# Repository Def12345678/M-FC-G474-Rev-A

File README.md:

# M-FC — Modular Flight Controller (REV-1)

> **Note:** This is REV-1 — a Proof-of-Concept / educational build. REV-2 is in development and will address known hardware ergonomics issues. Not recommended for production use.

M-FC has been flying on a 5" freestyle build for over a year.

---

## Overview

M-FC is a DIY flight controller designed for FPV drones 30.5x30.5mm mounting holes, built around the STM32G474RET6 microcontroller and running Betaflight 4.6. The "Modular" name reflects the connector philosophy — every peripheral interface is broken out via JST-SH connectors, making wiring clean, repeatable, and swap-friendly.

The board is paired with a dedicated PDB in a standard FC/PDB stack configuration. The FC itself operates at 5V (no onboard BEC), sourcing power from the ESC or PDB. REV-2 will include an onboard BEC.

---

## Hardware Specifications

| Component | Details |
|---|---|
| **MCU** | STM32G474RET6 |
| **IMU** | ICM-42688-P (SPI2) |
| **Barometer** | DPS368 (I2C4) |
| **Magnetometer** | Not populated |
| **OSD** | AT7456E (SPI1) |
| **Blackbox Flash** | W25Q128JVSIQ — 16 MB (SPI3) |
| **USB** | USB-C (with detect on PA10) |
| **Mounting** | 30.5 × 30.5 mm |
| **Input Voltage** | 5V (no onboard BEC — requires 5V from ESC or PDB) |

### Power Architecture

The FC does not regulate voltage from the battery. **5V must be supplied externally** — either from an ESC BEC or from the PDB — via the dedicated 5V pads on the board.

Two separate LDO regulators are present onboard:
- One for the MCU
- One for sensors (IMU, barometer)

A **Schottky diode** is used to isolate USB power from battery power. When powered via USB only, the FC supplies power exclusively to the MCU, sensors (IMU, barometer), OSD chip, flash, GPS, and RX. All remaining peripherals (motors, VTX, etc.) are only powered when the battery is connected via the PDB.

### PDB (Stack)

| Parameter | Value |
|---|---|
| **Max continuous current** | ~120 A total |
| **Per-motor channel** | ~30 A |
| **Configuration** | FC + PDB stack |

The FC connects to the PDB via an 8-pin JST-SH connector plus dedicated `5V_IN` and `GND` solder pads. The `5V_IN` pad powers the FC only — it does not back-feed to the PDB rail.

The PDB includes:
- **5V buck converter** — 2.5 A output
- **9V buck converter** — 2.5 A output (configurable to 12V by replacing resistor R5 — refer to the schematic for the correct resistor value via the linked Texas Instruments buck calculator)

Each ESC must be connected through the PDB. The `VBAT` pin on the 8-pin JST-SH outputs a voltage-divided signal safe for the MCU ADC, used for battery voltage monitoring in Betaflight.

---

## Connector Pinout

All peripheral connections use JST-SH connectors.

| Connector | Pins | Interface | Notes |
|---|---|---|---|
| **ESC** | 8 | DSHOT + telemetry | Motors 1–4 |
| **RX** | 4 | UART | RC receiver |
| **CAM** | 3 | Camera control | Analog camera |
| **VTX** | 4 | UART | Video transmitter |
| **GPS** | 6 | UART + I2C | GPS + compass |
| **LED** | 3 | LED strip | Addressable LEDs |

### Additional Exposed Pads

- **5V input pads** — mandatory external 5V supply
- **PWM 1–3** — additional PWM outputs
- **UART breakout** — spare UART pads
- **I2C breakout** — spare I2C pads

### Photos & Pinout Diagrams

Additional renders, routing views, and PCB previews are available in the [`img/`](img/) folder.

---

## Betaflight Target

- **Betaflight version:** 4.6
- **Target name:** `M-FC`
- **MCU family:** `STM32G47X`

Pre-compiled firmware (`.hex`) and the target config file are included in this repository. The hex supports all features listed below.

### Enabled Features

| Feature | Detail |
|---|---|
| Gyroscope / Accelerometer | ICM-42688-P via SPI2 |
| Barometer | DPS368 via I2C4 |
| Blackbox | W25Q128FV via SPI3, default device |
| OSD | MAX7456 (AT7456E) via SPI1 |
| Motors | DSHOT bitbang, pins PA0–PA3 |
| LED strip | PC0 |
| Buzzer | PC3 (inverted) |
| Debug LEDs | PB6, PB7, PB9 |
| VBAT ADC | PC1 |
| Current ADC | PC2 |
| Camera control | PB0 |
| GPS | Enabled |
| Magnetometer | Enabled (I2C2) |
| Position hold | Enabled |
| Altitude hold | Enabled |

### UART Map

| UART | TX | RX | Suggested Use |
|---|---|---|---|
| UART1 | PC4 | PC5 | — |
| UART3 | PB10 | PB11 | — |
| UART4 | PC10 | PC11 | — |
| UART5 | PC12 | PD2 | — |

### I2C Map

| Bus | SCL | SDA | Used for |
|---|---|---|---|
| I2C2 | PA8 | PA9 | Magnetometer |
| I2C3 | PC8 | PC9 | — |
| I2C4 | PC6 | PC7 | Barometer (DPS368) |

### Motor Timer Map

| Index | Pin | Timer | Channel |
|---|---|---|---|
| Motor 1 | PA0 | TIM2 | CH1 |
| Motor 2 | PA1 | TIM2 | CH2 |
| Motor 3 | PA2 | TIM2 | CH3 |
| Motor 4 | PA3 | TIM2 | CH4 |
| CC | PB0 | TIM3 | CH3 |
| LED strip | PC0 | — | CH1 |

---

## Flashing Firmware

### Pre-compiled hex

1. Download the `.hex` file from this repository.
2. Open **Betaflight Configurator 10.10+**.
3. Enter DFU mode — hold the boot button while plugging in USB-C, or send `bl` via CLI.
4. In the **Firmware Flasher** tab, select **Load Firmware [Local]** and pick the `.hex`.
5. Flash. Avoid **Full chip erase** unless necessary.

### Building from source

You can compile your own firmware with custom flags. Copy the target config file into the `configs/` folder of the Betaflight source tree, then build normally.

Building was tested using WSL. Refer to the official Betaflight build guide for setup instructions:
[https://betaflight.com/docs/development/building/Building-in-Ubuntu](https://betaflight.com/docs/development/building/Building-in-Ubuntu)

## Flight Logs & Blackbox Data

Blackbox logs and DVR footage from test flights are available in the [`logs/`](logs/) folder and on https://youtu.be/7Q5jRaf4V_Y(#) / https://pixeldrain.com/u/gxZJVt8E(#).

Logs were recorded using the onboard W25Q128JVSIQ flash via Betaflight 4.6 blackbox at 1kHz.

## Test build
| Component | Details |
|---|---|
| **ESC** | LittleBee Spring 30A (BlueJay firmware) |
| **VTX** | SpeedyBee TX800 (Pagoda2) |
| **RX** | SpeedyBee Nano ELRS |
| **Camera** | Mista 1672 |
| **Motors** | Emax RS2205 2350KV |
| **Battery** | 4S 1550mAh (Ovionic) |
| **Frame** | Geprc MK4 5" |

---

## Known Issues (REV-1)

- **Connector placement ergonomics** — JST-SH connectors are not optimally positioned for clean cable routing in a standard stack build. This is the primary driver for REV-2.
- **Betaflight 4.5 blackbox bug** — Blackbox was unreliable on Betaflight 4.5. Betaflight 4.6 resolves this; use 4.6 or later.
- **No onboard 5V BEC** — Requires external 5V source from ESC or PDB.

---

## Planned Changes (REV-2)

- Revised connector layout for improved cable management
- Onboard 5V BEC
- Additional ergonomic improvements based on REV-1 testing

---

## Acknowledgements

Thanks to [@awocrf](https://github.com/awocrf) for reviewing the schematic for correctness and readability, and for helping with PCB layout aesthetics.

---

## License

This project is released under the **MIT License**. See [LICENSE](LICENSE) for details.

Firmware is based on [Betaflight](https://github.com/betaflight/betaflight), licensed under **GPLv3**.

---

## Contributing

This is currently a personal/educational project. REV-2 is in active development. Issues and suggestions are welcome via GitHub Issues.

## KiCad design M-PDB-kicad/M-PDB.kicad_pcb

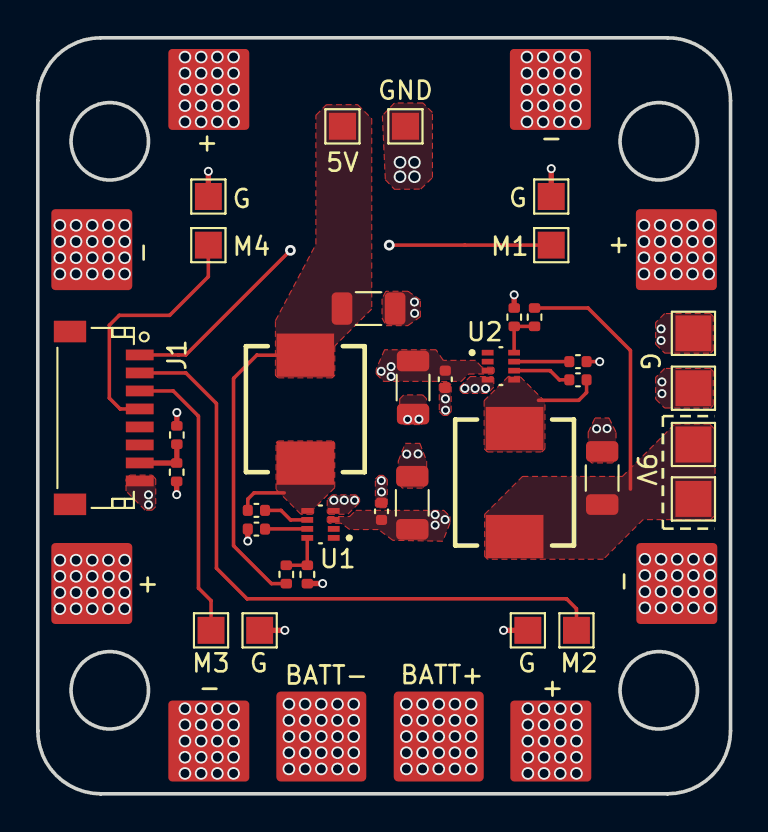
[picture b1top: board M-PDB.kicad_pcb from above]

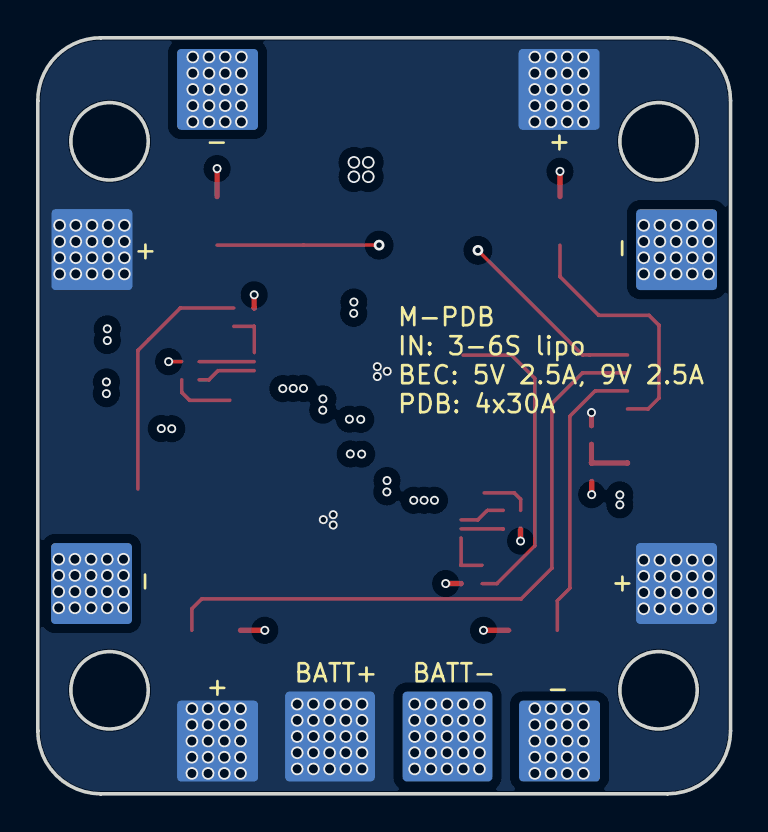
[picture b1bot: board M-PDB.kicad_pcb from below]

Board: 4 copper layers, 38.5 x 42.0 mm, 55 parts (10 on the bottom side), 17 nets.

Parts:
C1, C3, C6, C8: 100n; C_0402_1005Metric
C2, C4, C7, C9: 10u; C_1206_3216Metric
C5, C10: 33n; C_0402_1005Metric
J1: FC Conn; JST_SH_SM08B-SRSS-TB_08x1.00mm_Angled
L1: 6u8; IND-SMD_L7.0-W6.6
L2: 10u; IND-SMD_L7.0-W6.6
PAD1, PAD7: 12V; TestPoint_Pad_2.0x2.0mm
PAD2, PAD8: GND; TestPoint_Pad_2.0x2.0mm
PAD3: M1; TestPoint_Pad_1.5x1.5mm
PAD4, PAD6, PAD10, PAD12, PAD14: GND; TestPoint_Pad_1.5x1.5mm
PAD5: M2; TestPoint_Pad_1.5x1.5mm
PAD9: M3; TestPoint_Pad_1.5x1.5mm
PAD11: M4; TestPoint_Pad_1.5x1.5mm
PAD13: 5V; TestPoint_Pad_1.5x1.5mm
PAD15, PAD15#2: BATT+; pad5x5
PAD16, PAD16#2: BATT-; pad5x5
PAD17, PAD17#2: M1_PWR+; pad4.5
PAD18, PAD18#2: M1_PWR-; pad4.5
PAD19, PAD19#2: M3_PWR+; pad4.5
PAD20, PAD20#2: M3_PWR-; pad4.5
PAD21, PAD21#2: M2_PWR+; pad4.5
PAD22, PAD22#2: M2_PWR-; pad4.5
PAD23, PAD23#2: M4_PWR+; pad4.5
PAD24, PAD24#2: M4_PWR-; pad4.5
R1: 100K; R_0402_1005Metric
R2: 52K3; R_0402_1005Metric
R3, R4, R6: 10K; R_0402_1005Metric
R5: 102K; R_0402_1005Metric
U1, U2: TPS62933DRLR; SOTFL50P160X60-8N

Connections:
+5V: C4.1, L1.2, PAD13.1, R2.1
+9V: C9.1, L2.2, PAD1.1, PAD7.1, R5.1
+VBAT: C2.1, C3.1, C7.1, C8.1, PAD15.1, PAD15#2.1, PAD17.1, PAD17#2.1, PAD19.1, PAD19#2.1, PAD21.1, PAD21#2.1, PAD23.1, PAD23#2.1, R1.1, U1.3 (VIN), U2.3 (VIN)
/ADC_VBAT: J1.7, R1.2, R3.1
/BUCK2_BST: C6.1, U2.6 (BST)
/BUCK2_FB: R5.2, R6.1, U2.8 (FB)
/BUCK2_SS: C10.1, U2.7 (SS)
/BUCK2_SW: C6.2, L2.1, U2.5 (SW)
/BUCK_BST: C1.1, U1.6 (BST)
/BUCK_FB: R2.2, R4.1, U1.8 (FB)
/BUCK_SS: C5.1, U1.7 (SS)
/BUCK_SW: C1.2, L1.1, U1.5 (SW)
GND: C2.2, C3.2, C4.2, C5.2, C7.2, C8.2, C9.2, C10.2, J1.8, PAD2.1, PAD4.1, PAD6.1, PAD8.1, PAD10.1, PAD12.1, PAD14.1, PAD16.1, PAD16#2.1, PAD18.1, PAD18#2.1, PAD20.1, PAD20#2.1, PAD22.1, PAD22#2.1, PAD24.1, PAD24#2.1, R3.2, R4.2, R6.2, U1.4 (GND), U2.4 (GND)
M1: J1.1, PAD3.1
M2: J1.2, PAD5.1
M3: J1.3, PAD9.1
M4: J1.4, PAD11.1

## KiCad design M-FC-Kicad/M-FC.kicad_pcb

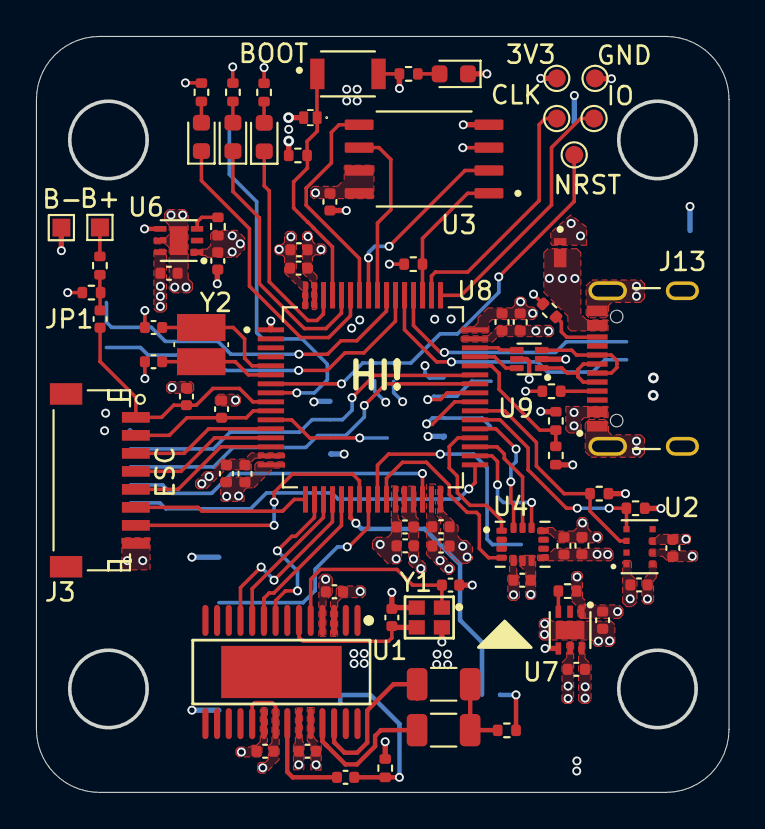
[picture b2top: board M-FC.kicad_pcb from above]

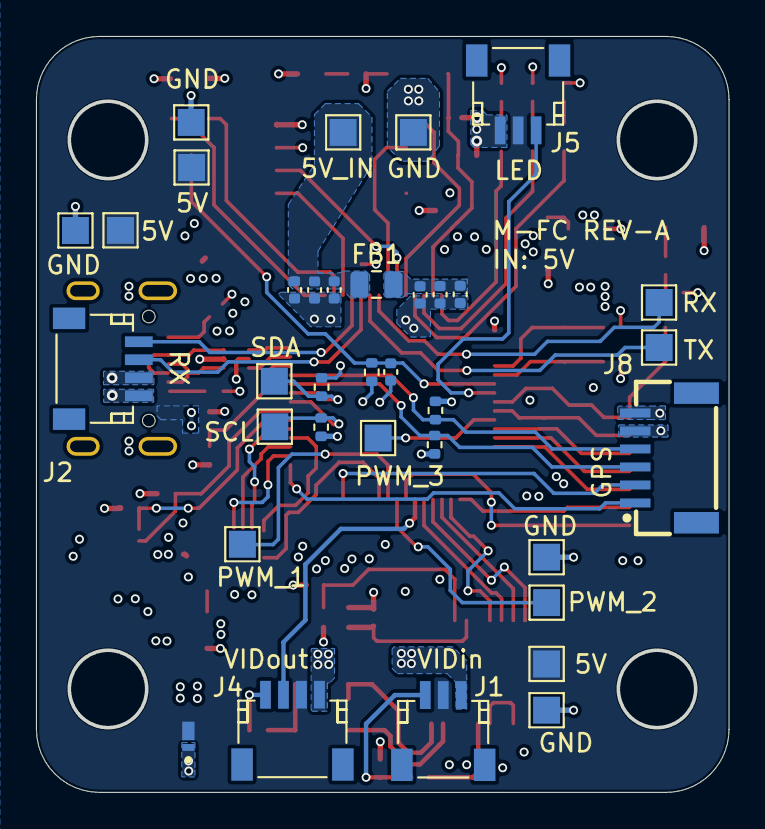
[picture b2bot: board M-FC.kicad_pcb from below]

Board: 4 copper layers, 38.5 x 42.0 mm, 112 parts (35 on the bottom side), 76 nets.

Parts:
C1, C2, C3, C4, C5, C6, C11, C13, C20, C30, C31, C32, C33, C34, C35, C36, C37, C38, C43: 100n; C_0402_1005Metric
C7, C8: 47u; C_1206_3216Metric
C9, C10, C39, C40: 10p; C_0402_1005Metric
C12: 2p2; C_0402_1005Metric
C14, C41, C42: 10n; C_0402_1005Metric
C19, C22, C24, C44: 10u; C_0402_1005Metric
C23, C25, C26, C27, C28, C29: 1u; C_0402_1005Metric
D1, D2: SDM2U30CSP-7B; DIO_SDM2U40CSP-7B
D10: Blue; LED_0603_1608Metric
D11: Green; LED_0603_1608Metric
D12: Amber; LED_0603_1608Metric
D14: ESD; ESDALC6V1-1U2
D18: RED; LED_0603_1608Metric
FB1: 300R; C_0805_2012Metric
J1: CAM; JST_SH_SM03B-SRSS-TB_03x1.00mm_Angled
J2: RX; JST_SH_SM04B-SRSS-TB_04x1.00mm_Angled
J3: ESC/PDB CONN; JST_SH_SM08B-SRSS-TB_08x1.00mm_Angled
J4: VTX; JST_SH_SM04B-SRSS-TB_04x1.00mm_Angled
J5: LED; JST_SH_SM03B-SRSS-TB_03x1.00mm_Angled
J8: GPS; CONN-SMD_6P-P1.00_XUNPU_WAFER-SH1.0-6PWB
J13: USB-C-16P; KINGHELM_KH-TYPE-C-16P
JP1: SolderJumper_2_Open; C_0402_1005Metric
PAD1, PAD2, PAD4: VCC; TestPoint_Pad_1.5x1.5mm
PAD3: PWM_3; TestPoint_Pad_1.5x1.5mm
PAD5: 5V_IN; TestPoint_Pad_1.5x1.5mm
PAD6, PAD7, PAD8, PAD9, PAD10: GND; TestPoint_Pad_1.5x1.5mm
PAD11: RX5; TestPoint_Pad_1.5x1.5mm
PAD12: TX5; TestPoint_Pad_1.5x1.5mm
PAD13: I2C3_SCL; TestPoint_Pad_1.5x1.5mm
PAD14: I2C3_SDA; TestPoint_Pad_1.5x1.5mm
PAD15: PWM_1; TestPoint_Pad_1.5x1.5mm
PAD16: PWM_2; TestPoint_Pad_1.5x1.5mm
PAD18: 3V3_CORE; TestPoint_Pad_D1.0mm
PAD19: SWDIO; TestPoint_Pad_D1.0mm
PAD20: SWDCLK; TestPoint_Pad_D1.0mm
PAD21: NRST; TestPoint_Pad_D1.0mm
PAD22: GND; TestPoint_Pad_D1.0mm
PAD23: VBAT; TestPoint_Pad_1.0x1.0mm
PAD24: GND; TestPoint_Pad_1.0x1.0mm
R1, R4: 75; R_0402_1005Metric
R2, R3, R8, R9, R10, R11, R12, R13, R21: 10k; R_0402_1005Metric
R5, R17, R19: 10K; R_0402_1005Metric
R14, R15, R16, R25: 1K; R_0402_1005Metric
R18, R20, R22: 100K; R_0402_1005Metric
R23, R24: 5K1; R_0402_1005Metric
SW1: BOOT0; SW_B3U-1000P
U1: AT7456E; TSSOP-28_L9.7-W4.4-P0.65-LS6.4-BL-EP-2
U2: DPS368XTSA1; XDCR_DPS368XTSA1
U3: W25Q128JVSIQ; SOIC127P790X216-8N
U4: ICM-42688-P; PQFN50P300X250X97-14N
U6, U7: LP5912-3.3DRV; SON65P200X200X80-7N
U8: STM32G474RET6; QFP50P1200X1200X160-64N
U9: USBLC6-2P6; SOT50P160X60-6N
Y1: 27MHz; CRYSTAL-SMD_4P-L2.0-W1.6-BL
Y2: 8MHz; XTAL_NX3225GD-8MHZ-STD-CRA-3

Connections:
+3V3_CORE: C11.2, C23.1, C26.1, C27.1, C28.1, C29.1, C30.1, C31.1, C32.1, C33.1, C34.1, C35.1, PAD18.1, R5.1, R8.1, R10.1, R11.1, R12.1, R13.1, R14.1, R15.1, R16.1, R17.1, R25.1, SW1.2, U3.3 (/WP(IO2)), U3.7 (/HOLD/RESET(IO3)), U3.8 (VCC), U6.1 (OUT), U8.1 (VBAT), U8.16 (VDD), U8.28 (VREF+), U8.29 (VDDA), U8.32 (VDD), U8.48 (VDD), U8.64 (VDD)
+3V3_SENS: C4.2, C5.2, C12.2, C13.2, C14.2, C25.1, R2.1, R3.1, R9.1, U2.6 (VDDIO), U2.8 (VDD), U4.5 (VDDIO), U4.8 (VDD), U7.1 (OUT)
+5V: C1.2, C2.1, C3.2, C22.1, C24.1, D1.1 (K), D2.1 (K), J2.3, J8.5, U1.3 (DVDD), U1.19 (~RESET), U1.21 (AVDD), U1.24 (PVDD), U6.4 (EN), U6.6 (IN), U7.4 (EN), U7.6 (IN)
+5V_REG: C19.1, C20.1, C42.1, D1.2 (A), FB1.2, J1.2, J4.3, J5.2, PAD1.1, PAD2.1, PAD4.1
+5V_UNFLT: C41.1, C43.1, C44.1, FB1.1, PAD5.1
+VBAT: PAD23.1, R18.1
/Connectors/ADC_CURR: C38.1, J3.2, U8.10 (PC2)
/Connectors/ADC_VBAT: C37.1, J3.1, JP1.2 (B), U8.9 (PC1)
/Connectors/I2C2_SCL: J8.3, R11.2, U8.42 (PA8)
/Connectors/I2C2_SDA: J8.4, R10.2, U8.43 (PA9)
/Connectors/I2C3_SCL: PAD13.1, R13.2, U8.40 (PC8)
/Connectors/I2C3_SDA: PAD14.1, R12.2, U8.41 (PC9)
/Connectors/LED_STRIP: J5.1, U8.8 (PC0)
/Connectors/M1: J3.3, U8.12 (PA0)
/Connectors/M2: J3.4, U8.13 (PA1)
/Connectors/M3: J3.5, U8.14 (PA2)
/Connectors/M4: J3.6, U8.17 (PA3)
/Connectors/PWM_1: PAD15.1, U8.25 (PB1)
/Connectors/PWM_2: PAD16.1, U8.24 (PB0)
/Connectors/PWM_3: PAD3.1, U8.11 (PC3)
/Connectors/RX1: J3.7, U8.23 (PC5)
/Connectors/RX3: J8.1, U8.33 (PB11)
/Connectors/RX4: J2.2, U8.53 (PC11)
/Connectors/RX5: PAD11.1, U8.55 (PD2)
/Connectors/TX1: J4.2, U8.22 (PC4)
/Connectors/TX3: J8.2, U8.30 (PB10)
/Connectors/TX4: J2.1, U8.52 (PC10)
/Connectors/TX5: PAD12.1, U8.54 (PC12)
/Connectors/VIDEO_IN: C6.2, J1.1, R1.2
/Connectors/VIDEO_OUT: J4.1, R4.2
/MCU/BOOT: D14.1, R21.2, SW1.1, U8.61 (PB8-BOOT0)
/MCU/HSE_IN: C40.2, U8.5 (PF0-OSC_IN), Y2.1
/MCU/HSE_OUT: C39.1, U8.6 (PF1-OSC_OUT), Y2.2
/MCU/I2C4_SCL: R3.2, U2.4 (SCK), U8.38 (PC6)
/MCU/I2C4_SDA: R2.2, U2.3 (SDI), U8.39 (PC7)
/MCU/IMU_IRQ: U4.4 (INT1/INT), U8.26 (PB2)
/MCU/LED_A: D12.1 (K), U8.60 (PB7)
/MCU/LED_A_R: D12.2 (A), R16.2
/MCU/LED_B: D10.1 (K), U8.62 (PB9)
/MCU/LED_B_R: D10.2 (A), R14.2
/MCU/LED_G: D11.1 (K), U8.59 (PB6)
/MCU/LED_G_R: D11.2 (A), R15.2
/MCU/LED_PWR: D18.2 (A), R25.2
/MCU/MCU_USB_DN: U8.45 (PA11), U9.6 (I/O1)
/MCU/MCU_USB_DP: U8.46 (PA12), U9.4 (I/O2)
/MCU/NRST: C36.1, PAD21.1, R17.2, U8.7 (PG10-~RST)
/MCU/PAD_VBAT: JP1.1 (A), R18.2, R19.1
/MCU/SPI1_CS: U1.8 (~CS), U8.18 (PA4)
/MCU/SPI1_MISO: U1.11 (SDOUT), U8.20 (PA6)
/MCU/SPI1_MOSI: U1.9 (SDIN), U8.21 (PA7)
/MCU/SPI1_SCK: U1.10 (SCLK), U8.19 (PA5)
/MCU/SPI2_CS: U4.12 (AP_CS), U8.34 (PB12)
/MCU/SPI2_MISO: U4.1 (AP_SDO/AP_AD0), U8.36 (PB14)
/MCU/SPI2_MOSI: U4.14 (AP_SDA/AP_SDIO/AP_SDI), U8.37 (PB15)
/MCU/SPI2_SCK: U4.13 (AP_SCL/AP_SCLK), U8.35 (PB13)
/MCU/SPI3_CS: R5.2, U3.1 (/CS), U8.51 (PA15)
/MCU/SPI3_MISO: U3.2 (DO(IO1)), U8.57 (PB4)
/MCU/SPI3_MOSI: U3.5 (DI(IO0)), U8.58 (PB5)
/MCU/SPI3_SCK: U3.6 (CLK), U8.56 (PB3)
/MCU/SWDCLK: PAD20.1, U8.50 (PA14)
/MCU/SWDIO: PAD19.1, U8.49 (PA13)
/MCU/USB_CC1: J13.A5 (CC1), R23.2
/MCU/USB_CC2: J13.B5 (CC2), R24.1
/MCU/USB_DN: J13.A7 (DN1), J13.B7 (DN2), U9.1 (I/O1)
/MCU/USB_DP: J13.A6 (DP1), J13.B6 (DP2), U9.3 (I/O2)
/MCU/USB_SENS: R20.1, R22.2, U8.44 (PA10)
/Power supply/LDO_C_PG: R8.2, U6.3 (PG)
/Power supply/LDO_S_PG: R9.2, U7.3 (PG)
/Sensors & IC/OSD_CLKIN: C9.1, U1.5 (CLKIN), Y1.1
/Sensors & IC/OSD_SAG: C8.1, U1.25 (SAG)
/Sensors & IC/OSD_VIN: C6.1, U1.22 (VIN)
/Sensors & IC/OSD_VOUT: C7.1, U1.26 (VOUT)
/Sensors & IC/OSD_VOUT_R: C7.2, C8.2, R4.1
/Sensors & IC/OSD_XFB: C10.1, U1.6 (XFB), Y1.3
GND: C1.1, C2.2, C3.1, C4.1, C5.1, C9.2, C10.2, C11.1, C12.1, C13.1, C14.1, C19.2, C20.2, C22.2, C23.2, C24.2, C25.2, C26.2, C27.2, C28.2, C29.2, C30.2, C31.2, C32.2, C33.2, C34.2, C35.2, C36.2, C37.2, C38.2, C39.2, C40.1, C41.2, C42.2, C43.2, C44.2, D14.2, D18.1 (K), J1.3, J2.4, J3.8, J4.4, J5.3, J8.6, J13.A1_B12 (GND), J13.A12_B1 (GND), J13.SH1 (SHIELD), J13.SH2 (SHIELD), J13.SH3 (SHIELD), J13.SH4 (SHIELD), PAD6.1, PAD7.1, PAD8.1, PAD9.1, PAD10.1, PAD22.1, PAD24.1, R1.1, R19.2, R21.1, R22.1, R23.1, R24.2, U1.4 (DGND), U1.20 (AGND), U1.23 (PGND), U2.1 (GND), U2.7 (GND), U3.4 (GND), U4.6 (GND), U4.7 (RESV_7), U4.11 (RESV_11), U6.5 (GND), U6.7 (EP), U7.5 (GND), U7.7 (EP), U8.15 (VSS), U8.27 (VSSA), U8.31 (VSS), U8.47 (VSS), U8.63 (VSS), U9.2 (GND), Y1.2, Y1.4
VBUS: D2.2 (A), J13.A4_B9 (VBUS), J13.A9_B4 (VBUS), R20.2, U9.5 (VBUS)

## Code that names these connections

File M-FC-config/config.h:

/*
 * This file is part of Betaflight.
 *
 * Betaflight is free software. You can redistribute this software
 * and/or modify this software under the terms of the GNU General
 * Public License as published by the Free Software Foundation,
 * either version 3 of the License, or (at your option) any later
 * version.
 *
 * Betaflight is distributed in the hope that it will be useful,
 * but WITHOUT ANY WARRANTY; without even the implied warranty of
 * MERCHANTABILITY or FITNESS FOR A PARTICULAR PURPOSE.
 *
 * See the GNU General Public License for more details.
 *
 * You should have received a copy of the GNU General Public
 * License along with this software.
 *
 * If not, see <http://www.gnu.org/licenses/>.
 
 It's for testing purpose for new Open source FC
 */

#pragma once

#define FC_TARGET_MCU     STM32G47X

#define BOARD_NAME        M-FC
#define MANUFACTURER_ID   Cust


 //IMU
#define USE_ACC
#define USE_ACC_SPI_ICM42688P
#define USE_GYRO
#define USE_GYRO_SPI_ICM42688P

#define GYRO_1_EXTI_PIN                 PB2
#define USE_GYRO_EXTI
#define GYRO_1_CS_PIN                   PB12
#define SPI2_SCK_PIN                    PB13
#define SPI2_SDI_PIN                    PB14
#define SPI2_SDO_PIN                    PB15

#define GYRO_1_SPI_INSTANCE             SPI2

#define GYRO_1_ALIGN                    CW90_DEG

 //BARO
#define USE_BARO
#define USE_BARO_DPS310

#define I2C4_SCL_PIN                    PC6
#define I2C4_SDA_PIN                    PC7

#define BARO_I2C_INSTANCE               I2CDEV_4
#define DEFAULT_BARO_I2C_ADDRESS        119

 //FLASH
#define USE_FLASH
#define USE_FLASH_W25Q128FV

#define FLASH_CS_PIN                    PA15
#define SPI3_SCK_PIN                    PB3
#define SPI3_SDI_PIN                    PB4
#define SPI3_SDO_PIN                    PB5

#define FLASH_SPI_INSTANCE              SPI3

#define DEFAULT_BLACKBOX_DEVICE         BLACKBOX_DEVICE_FLASH


 //OSD
#define USE_MAX7456

#define MAX7456_SPI_CS_PIN   			PA4
#define SPI1_SCK_PIN                    PA5
#define SPI1_SDI_PIN                    PA6
#define SPI1_SDO_PIN                    PA7

#define MAX7456_SPI_INSTANCE SPI1

 //USB
#define USB_DETECT_PIN       PA10

 //MOTOR & PWM
#define MOTOR1_PIN           PA0
#define MOTOR2_PIN           PA1
#define MOTOR3_PIN           PA2
#define MOTOR4_PIN           PA3


#define USE_DSHOT
#define DEFAULT_DSHOT_BITBANG DSHOT_BITBANG_ON

 //LED STRIP 
#define USE_LED_STRIP
#define LED_STRIP_PIN        PC0

 //Buzzer
#define BEEPER_PIN           PC3  
#define BEEPER_INVERTED

 //DEBUG LED
#define LED0_PIN             PB7
#define LED1_PIN             PB6
#define LED2_PIN             PB9

 //ADC
#define ADC_VBAT_PIN         PC1
#define ADC_CURR_PIN         PC2

#define DEFAULT_VOLTAGE_METER_SOURCE    VOLTAGE_METER_ADC
#define DEFAULT_VOLTAGE_METER_SCALE     110

#define ADC1_DMA_OPT        1

 //ADDITIONAL RESOURCES
#define UART1_TX_PIN         PC4
#define UART1_RX_PIN         PC5

#define UART3_TX_PIN         PB10
#define UART3_RX_PIN         PB11

#define UART4_TX_PIN         PC10
#define UART4_RX_PIN         PC11

#define UART5_TX_PIN         PC12
#define UART5_RX_PIN         PD2

#define I2C2_SCL_PIN         PA8
#define I2C2_SDA_PIN         PA9

#define I2C3_SCL_PIN         PC8
#define I2C3_SDA_PIN         PC9

 //GPS
#define USE_GPS
 
 //MAG
#define USE_MAG
#define MAG_I2C_INSTANCE I2CDEV_2
 
 //Camera Control
#define USE_CAMERA_CONTROL
#define CAMERA_CONTROL_PIN PB0

 
 //POSITION HOLD & ALTITUDE
#define USE_POSITION_HOLD
#define USE_ALTITUDE_HOLD
 
 
 //TIMER MAP
#define TIMER_PIN_MAPPING \
	TIMER_PIN_MAP( 0, MOTOR1_PIN , 2,  1) \
    TIMER_PIN_MAP( 1, MOTOR2_PIN , 2,  2) \
    TIMER_PIN_MAP( 2, MOTOR3_PIN , 2,  3) \
    TIMER_PIN_MAP( 3, MOTOR4_PIN , 2,  4) \
    TIMER_PIN_MAP( 4, CAMERA_CONTROL_PIN , 3,  3) \
	TIMER_PIN_MAP( 5, LED_STRIP_PIN , 1,  1) 

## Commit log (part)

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2026-05-13 Add CERN Open Hardware Licence Version 2
    Added the CERN Open Hardware Licence Version 2 - Permissive to the project.
2026-05-15 Create .gitignore for KiCad project
    Add .gitignore for KiCad project files and temporary files
2026-05-15 Create img
2026-05-15 Create M-PDB-img
2026-05-15 Add MIT License to the project
2026-05-15 Update config.h for FC
2026-05-15 Revise README for Modular Flight Controller REV-1
    Updated README to reflect changes for REV-1, including detailed specifications, power architecture, and known issues.
2026-05-17 Add Flight Logs & Blackbox Data section to README
    Added section for Flight Logs and Blackbox Data with links.
2026-05-17 Add test build section to README
    Added a test build section with component details.
2026-05-20 Add mounting hole dimensions to overview
    Updated the overview section to include mounting hole dimensions.
2026-05-20 Update README with flight experience and image
    Added note about M-FC's flight experience and included an image.
